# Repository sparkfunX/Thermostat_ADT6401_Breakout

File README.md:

SparkFun Auto-Digital Thermostat - ADT6401
=============================

New from SparkX, the ADT6401 breakout board. This IC triggers alarm pin and LED when the temperature reading crosses a temperature trip point. Set the trip point easily using the SPDT switches included on the breakout.

SparkFun labored with love to design this board. Feel like supporting open-source hardware?
Buy a [board](https://www.sparkfun.com/) from SparkFun!

Repository Contents
-------------------

* **/Documents** - Datasheet for the ADT6401 IC.
* **/Hardware** - Eagle design files (.brd, .sch).
* **/Production** - Production panel files (.brd).

License Information
-------------------

This product is _**open source**_!

Please review the LICENSE.md file for license information.

If you have any questions or concerns regarding our licensing, please contact technical support on our [SparkFun Forum](https://www.sparkfun.com/viewforum.php?f=152).

Distributed as-is; no warranty is given.

- Your friends at SparkFun

_<COLLABORATION CREDIT>_

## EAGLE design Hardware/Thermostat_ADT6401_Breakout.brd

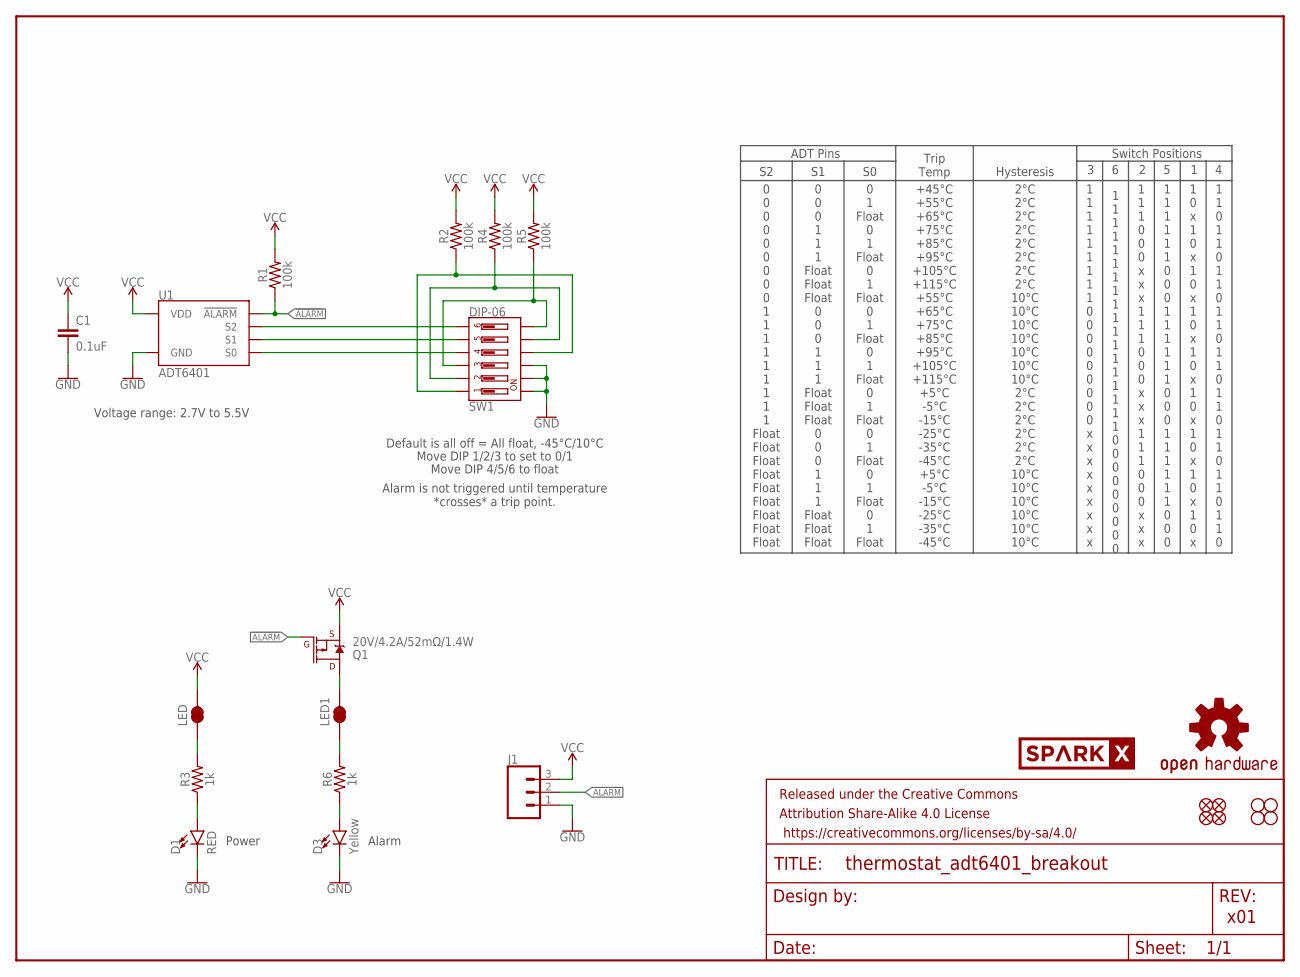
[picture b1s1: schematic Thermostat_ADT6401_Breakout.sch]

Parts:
C1: 0.1uF; 0603
D1: RED; LED-0603
D3: Yellow; LED-0603
FRAME1: FRAME-LETTER; CREATIVE_COMMONS
J1: CONN_031X03_NO_SILK; 1X03_NO_SILK
JP1, JP2, JP5, JP6: FIDUCIAL1X2; FIDUCIAL-1X2
JP3, JP4, JP8, JP9: STAND-OFF
LED, LED1: JUMPER-SMT_2_NC_TRACE_SILK; SMT-JUMPER_2_NC_TRACE_SILK
LOGO1: OSHW-LOGOMINI; OSHW-LOGO-MINI
Q1: 20V/4.2A/52mΩ/1.4W; SOT23-3
R1, R2, R4, R5: 100k; 0603
R3, R6: 1k; 0603
SW1: DIP-06; DIPSWITCH-06-SMD
U1: ADT6401; SOT23-6
U$1: SPARKX-LOGO4; SPARKX-MEDIUM

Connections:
!ALARM!: J1.2, Q1.1 (G), R1.1, U1.6 (!ALARM!)
GND: C1.2, D1.C, D3.C, J1.1, SW1.10, SW1.11, SW1.12, U1.5 (GND)
unnamed: D1.A, R3.1
unnamed: LED.1, R3.2
unnamed: LED1.2, Q1.3 (D)
unnamed: D3.A, R6.1
unnamed: LED1.1, R6.2
S0: SW1.4, U1.3 (S0)
S0_PU: R2.1, SW1.1, SW1.9
S1: SW1.5, U1.2 (S1)
S1_PU: R4.1, SW1.2, SW1.8
S2: SW1.6, U1.1 (S2)
S2_PU: R5.1, SW1.3, SW1.7
VCC: C1.1, J1.3, LED.2, Q1.2 (S), R1.2, R2.2, R4.2, R5.2, U1.4 (VDD)

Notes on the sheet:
x01
Power
Move DIP 4/5/6 to float
0 0 0 0 0 0 0 0 0 1 1 1 1 1 1 1 1 1 Float Float Float Float Float Float Float Float Float
+45°C +55°C +65°C +75°C +85°C +95°C +105°C +115°C +55°C +65°C +75°C +85°C +95°C +105°C +115°C +5°C -5°C -15°C -25°C -35°C -45°C +5°C -5°C -15°C -25°C -35°C -45°C
0 0 0 1 1 1 Float Float Float 0 0 0 1 1 1 Float Float Float 0 0 0 1 1 1 Float Float Float
0 1 Float 0 1 Float 0 1 Float 0 1 Float 0 1 Float 0 1 Float 0 1 Float 0 1 Float 0 1 Float
2°C 2°C 2°C 2°C 2°C 2°C 2°C 2°C 10°C 10°C 10°C 10°C 10°C 10°C 10°C 2°C 2°C 2°C 2°C 2°C 2°C 10°C 10°C 10°C 10°C 10°C 10°C
Trip Temp
Hysteresis
Move DIP 1/2/3 to set to 0/1
Default is all off = All float, -45°C/10°C
Alarm
Voltage range: 2.7V to 5.5V
Switch Positions
1 1 0 1 1 0 1 1 0 1 1 0 1 1 0 1 1 0 1 1 0 1 1 0 1 1 0
1 0 x 1 0 x 1 0 x 1 0 x 1 0 x 1 0 x 1 0 x 1 0 x 1 0 x
1 1 1 1 1 1 0 0 0 1 1 1 1 1 1 0 0 0 1 1 1 1 1 1 0 0 0
1 1 1 0 0 0 x x x 1 1 1 0 0 0 x x x 1 1 1 0 0 0 x x x
1 1 1 1 1 1 1 1 1 1 1 1 1 1 1 1 1 1 0 0 0 0 0 0 0 0 0
1 1 1 1 1 1 1 1 1 0 0 0 0 0 0 0 0 0 x x x x x x x x x
ADT Pins
Alarm is not triggered until temperature *crosses* a trip point.

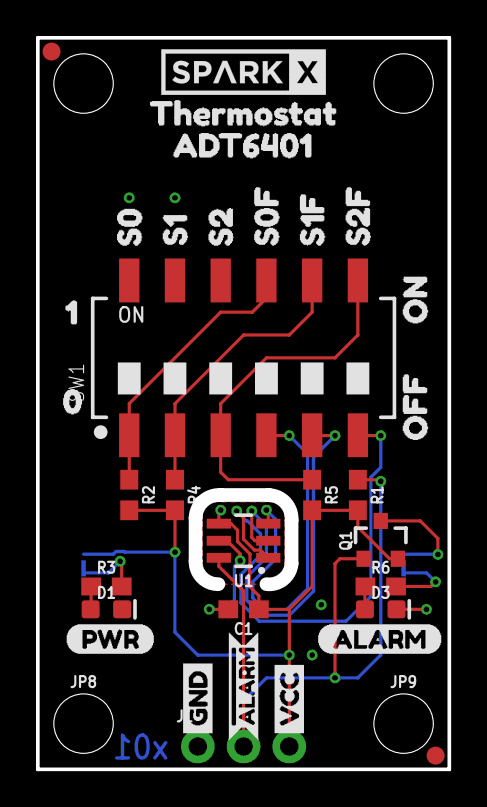
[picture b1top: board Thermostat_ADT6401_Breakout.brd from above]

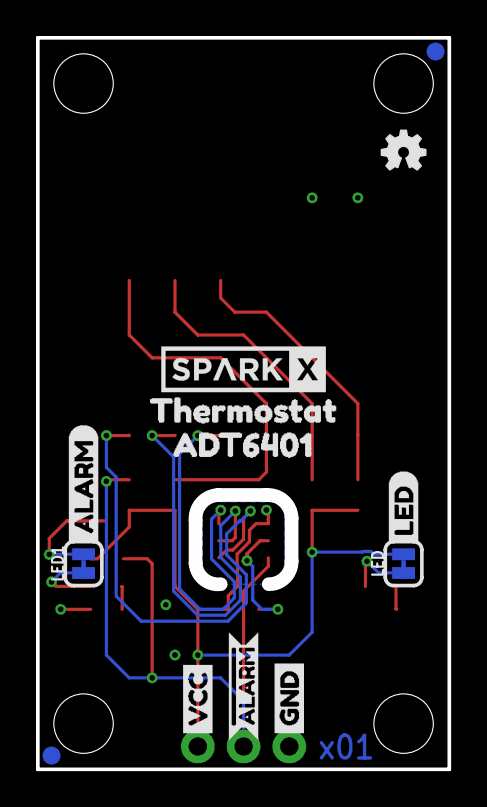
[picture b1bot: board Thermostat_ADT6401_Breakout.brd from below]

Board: 2 copper layers, 22.3 x 40.1 mm, 52 parts (13 on the bottom side), 14 nets.

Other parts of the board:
U$2: 01
U$3, U$15: #ALARM6
U$4, U$12: ADT64012
U$5, U$13: GND6
U$6: OFF3
U$7: ON2
U$8: 10
U$9, U$19: THERMOSTAT0
U$10: (PWR)
U$11, U$16: VCC5
U$14: S1F5
U$17: SPARKX-LOGO4; SPARKX-MEDIUM
U$18: ORDERING_INSTRUCTIONS
U$20: ALARM1
U$21: S2F7
U$22: S12
U$23: S23
U$24: S00
U$25: S0F1
U$26: LED0
U$27: ALARM2

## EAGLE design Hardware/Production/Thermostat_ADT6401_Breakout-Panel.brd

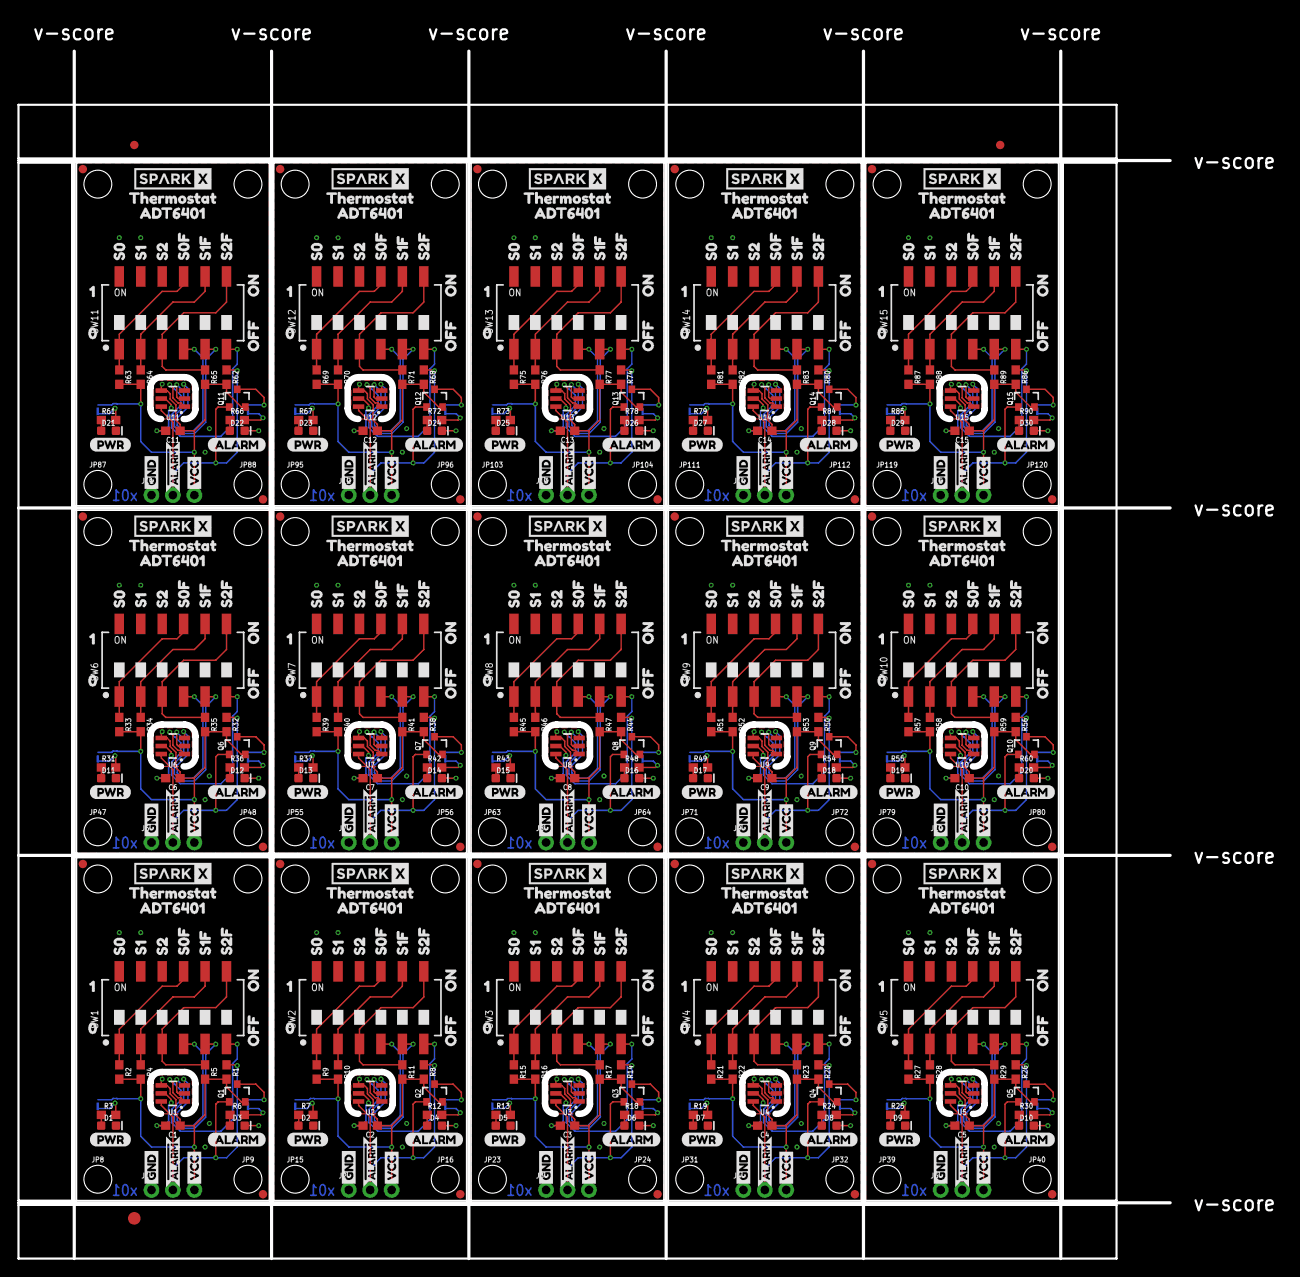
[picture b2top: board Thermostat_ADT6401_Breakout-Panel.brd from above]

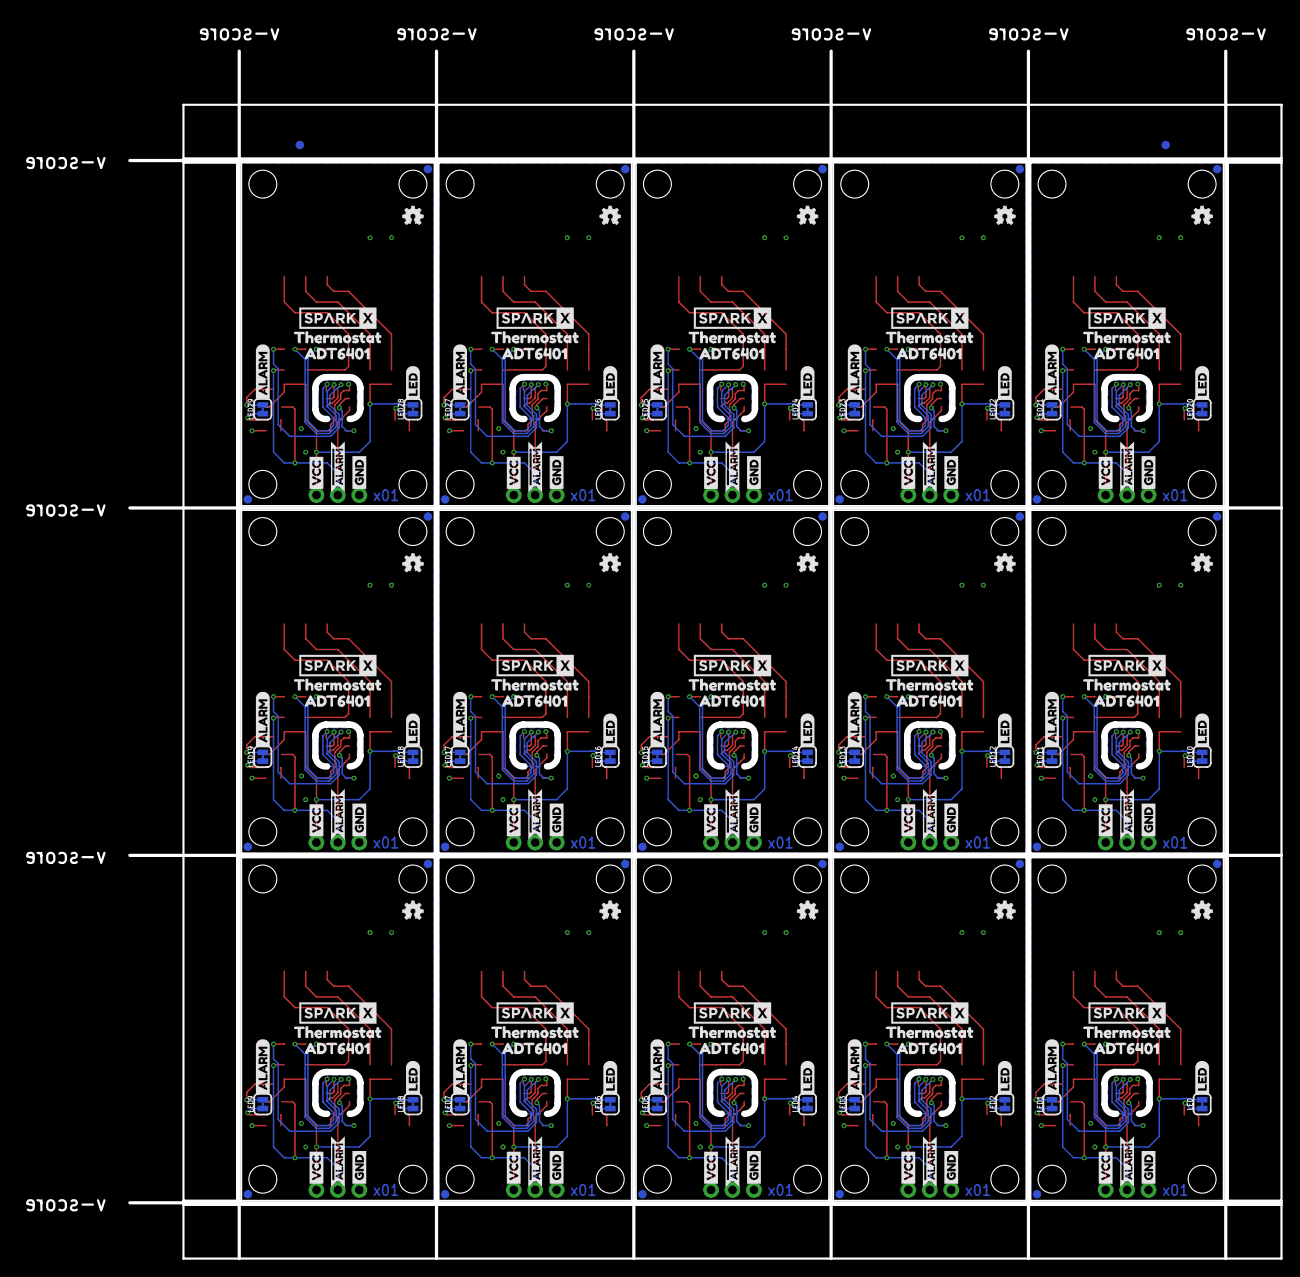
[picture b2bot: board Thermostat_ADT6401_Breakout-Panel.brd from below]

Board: 2 copper layers, 149.2 x 146.5 mm, 755 parts (197 on the bottom side), 210 nets.

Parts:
C1, C2, C3, C4, C5, C6, C7, C8, C9, C10, C11, C12, C13, C14, C15: 0.1uF; 0603
D1, D2, D5, D7, D9, D11, D13, D15, D17, D19, D21, D23, D25, D27, D29: RED; LED-0603
D3, D4, D6, D8, D10, D12, D14, D16, D18, D20, D22, D24, D26, D28, D30: Yellow; LED-0603
E$1, E$2, E$3, E$4: FIDUCIAL-1X2
E$5: FIDUCIAL-1.5X3
J1, J2, J3, J4, J5, J6, J7, J8, J9, J10, J11, J12, J13, J14, J15: 1X03_NO_SILK
JP1, JP2, JP5, JP6, JP11, JP12, JP13, JP14, JP19, JP20, JP21, JP22, JP27, JP28, JP29, JP30, JP35, JP36, JP37, JP38, JP43, JP44, JP45, JP46, JP51, JP52, JP53, JP54, JP59, JP60, JP61, JP62, JP67, JP68, JP69, JP70, JP75, JP76, JP77, JP78, JP83, JP84, JP85, JP86, JP91, JP92, JP93, JP94, JP99, JP100, JP101, JP102, JP107, JP108, JP109, JP110, JP115, JP116, JP117, JP118: FIDUCIAL1X2; FIDUCIAL-1X2
JP3, JP4, JP7, JP8, JP9, JP10, JP15, JP16, JP17, JP18, JP23, JP24, JP25, JP26, JP31, JP32, JP33, JP34, JP39, JP40, JP41, JP42, JP47, JP48, JP49, JP50, JP55, JP56, JP57, JP58, JP63, JP64, JP65, JP66, JP71, JP72, JP73, JP74, JP79, JP80, JP81, JP82, JP87, JP88, JP89, JP90, JP95, JP96, JP97, JP98, JP103, JP104, JP105, JP106, JP111, JP112, JP113, JP114, JP119, JP120: STAND-OFF
LED, LED1, LED2, LED3, LED4, LED5, LED6, LED7, LED8, LED9, LED10, LED11, LED12, LED13, LED14, LED15, LED16, LED17, LED18, LED19, LED20, LED21, LED22, LED23, LED24, LED25, LED26, LED27, LED28, LED29: SMT-JUMPER_2_NC_TRACE_SILK
LOGO1, LOGO2, LOGO3, LOGO4, LOGO5, LOGO6, LOGO7, LOGO8, LOGO9, LOGO10, LOGO11, LOGO12, LOGO13, LOGO14, LOGO15: OSHW-LOGOMINI; OSHW-LOGO-MINI
Q1, Q2, Q3, Q4, Q5, Q6, Q7, Q8, Q9, Q10, Q11, Q12, Q13, Q14, Q15: 20V/4.2A/52mΩ/1.4W; SOT23-3
R1, R2, R4, R5, R8, R9, R10, R11, R14, R15, R16, R17, R20, R21, R22, R23, R26, R27, R28, R29, R32, R33, R34, R35, R38, R39, R40, R41, R44, R45, R46, R47, R50, R51, R52, R53, R56, R57, R58, R59, R62, R63, R64, R65, R68, R69, R70, R71, R74, R75, R76, R77, R80, R81, R82, R83, R86, R87, R88, R89: 100k; 0603
R3, R6, R7, R12, R13, R18, R19, R24, R25, R30, R31, R36, R37, R42, R43, R48, R49, R54, R55, R60, R61, R66, R67, R72, R73, R78, R79, R84, R85, R90: 1k; 0603
SW1, SW2, SW3, SW4, SW5, SW6, SW7, SW8, SW9, SW10, SW11, SW12, SW13, SW14, SW15: DIP-06; DIPSWITCH-06-SMD
U1, U2, U3, U4, U5, U6, U7, U8, U9, U10, U11, U12, U13, U14, U15: ADT6401; SOT23-6
U$1, U$17, U$18, U$36, U$53, U$62, U$79, U$88, U$105, U$114, U$131, U$140, U$157, U$166, U$183, U$192, U$209, U$218, U$235, U$244, U$261, U$270, U$287, U$296, U$313, U$322, U$339, U$348, U$365, U$374: SPARKX-LOGO4; SPARKX-MEDIUM
U$2, U$40, U$66, U$92, U$118, U$144, U$170, U$196, U$222, U$248, U$274, U$300, U$326, U$352, U$378: 01
U$3, U$15, U$38, U$39, U$64, U$65, U$90, U$91, U$116, U$117, U$142, U$143, U$168, U$169, U$194, U$195, U$220, U$221, U$246, U$247, U$272, U$273, U$298, U$299, U$324, U$325, U$350, U$351, U$376, U$377: #ALARM6
U$4, U$12, U$49, U$50, U$75, U$76, U$101, U$102, U$127, U$128, U$153, U$154, U$179, U$180, U$205, U$206, U$231, U$232, U$257, U$258, U$283, U$284, U$309, U$310, U$335, U$336, U$361, U$362, U$387, U$388: ADT64012
U$5, U$13, U$29, U$34, U$55, U$60, U$81, U$86, U$107, U$112, U$133, U$138, U$159, U$164, U$185, U$190, U$211, U$216, U$237, U$242, U$263, U$268, U$289, U$294, U$315, U$320, U$341, U$346, U$367, U$372: GND6
U$6, U$30, U$56, U$82, U$108, U$134, U$160, U$186, U$212, U$238, U$264, U$290, U$316, U$342, U$368: OFF3
U$7, U$31, U$57, U$83, U$109, U$135, U$161, U$187, U$213, U$239, U$265, U$291, U$317, U$343, U$369: ON2
U$8, U$41, U$67, U$93, U$119, U$145, U$171, U$197, U$223, U$249, U$275, U$301, U$327, U$353, U$379: 10
U$9, U$19, U$32, U$37, U$58, U$63, U$84, U$89, U$110, U$115, U$136, U$141, U$162, U$167, U$188, U$193, U$214, U$219, U$240, U$245, U$266, U$271, U$292, U$297, U$318, U$323, U$344, U$349, U$370, U$375: THERMOSTAT0
U$10, U$28, U$54, U$80, U$106, U$132, U$158, U$184, U$210, U$236, U$262, U$288, U$314, U$340, U$366: (PWR)
U$11, U$16, U$33, U$35, U$59, U$61, U$85, U$87, U$111, U$113, U$137, U$139, U$163, U$165, U$189, U$191, U$215, U$217, U$241, U$243, U$267, U$269, U$293, U$295, U$319, U$321, U$345, U$347, U$371, U$373: VCC5
U$14, U$42, U$68, U$94, U$120, U$146, U$172, U$198, U$224, U$250, U$276, U$302, U$328, U$354, U$380: S1F5
U$20, U$51, U$77, U$103, U$129, U$155, U$181, U$207, U$233, U$259, U$285, U$311, U$337, U$363, U$389: ALARM1
U$21, U$43, U$69, U$95, U$121, U$147, U$173, U$199, U$225, U$251, U$277, U$303, U$329, U$355, U$381: S2F7
U$22, U$44, U$70, U$96, U$122, U$148, U$174, U$200, U$226, U$252, U$278, U$304, U$330, U$356, U$382: S12
U$23, U$45, U$71, U$97, U$123, U$149, U$175, U$201, U$227, U$253, U$279, U$305, U$331, U$357, U$383: S23
U$24, U$46, U$72, U$98, U$124, U$150, U$176, U$202, U$228, U$254, U$280, U$306, U$332, U$358, U$384: S00
U$25, U$47, U$73, U$99, U$125, U$151, U$177, U$203, U$229, U$255, U$281, U$307, U$333, U$359, U$385: S0F1
U$26, U$52, U$78, U$104, U$130, U$156, U$182, U$208, U$234, U$260, U$286, U$312, U$338, U$364, U$390: LED0
U$27, U$48, U$74, U$100, U$126, U$152, U$178, U$204, U$230, U$256, U$282, U$308, U$334, U$360, U$386: ALARM2

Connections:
!ALARM!: J1.2, Q1.1, R1.1, U1.6
!ALARM!1: J2.2, Q2.1, R8.1, U2.6
!ALARM!2: J3.2, Q3.1, R14.1, U3.6
!ALARM!3: J4.2, Q4.1, R20.1, U4.6
!ALARM!4: J5.2, Q5.1, R26.1, U5.6
!ALARM!5: J6.2, Q6.1, R32.1, U6.6
!ALARM!6: J7.2, Q7.1, R38.1, U7.6
!ALARM!7: J8.2, Q8.1, R44.1, U8.6
!ALARM!8: J9.2, Q9.1, R50.1, U9.6
!ALARM!9: J10.2, Q10.1, R56.1, U10.6
!ALARM!10: J11.2, Q11.1, R62.1, U11.6
!ALARM!11: J12.2, Q12.1, R68.1, U12.6
!ALARM!12: J13.2, Q13.1, R74.1, U13.6
!ALARM!13: J14.2, Q14.1, R80.1, U14.6
!ALARM!14: J15.2, Q15.1, R86.1, U15.6
GND: C1.2, D1.C, D3.C, J1.1, SW1.10, SW1.11, SW1.12, U1.5
GND1: C2.2, D2.C, D4.C, J2.1, SW2.10, SW2.11, SW2.12, U2.5
GND2: C3.2, D5.C, D6.C, J3.1, SW3.10, SW3.11, SW3.12, U3.5
GND3: C4.2, D7.C, D8.C, J4.1, SW4.10, SW4.11, SW4.12, U4.5
GND4: C5.2, D9.C, D10.C, J5.1, SW5.10, SW5.11, SW5.12, U5.5
GND5: C6.2, D11.C, D12.C, J6.1, SW6.10, SW6.11, SW6.12, U6.5
GND6: C7.2, D13.C, D14.C, J7.1, SW7.10, SW7.11, SW7.12, U7.5
GND7: C8.2, D15.C, D16.C, J8.1, SW8.10, SW8.11, SW8.12, U8.5
GND8: C9.2, D17.C, D18.C, J9.1, SW9.10, SW9.11, SW9.12, U9.5
GND9: C10.2, D19.C, D20.C, J10.1, SW10.10, SW10.11, SW10.12, U10.5
GND10: C11.2, D21.C, D22.C, J11.1, SW11.10, SW11.11, SW11.12, U11.5
GND11: C12.2, D23.C, D24.C, J12.1, SW12.10, SW12.11, SW12.12, U12.5
GND12: C13.2, D25.C, D26.C, J13.1, SW13.10, SW13.11, SW13.12, U13.5
GND13: C14.2, D27.C, D28.C, J14.1, SW14.10, SW14.11, SW14.12, U14.5
GND14: C15.2, D29.C, D30.C, J15.1, SW15.10, SW15.11, SW15.12, U15.5
unnamed: D2.A, R7.1
unnamed: LED2.1, R7.2
unnamed: D1.A, R3.1
unnamed: LED.1, R3.2
unnamed: LED1.2, Q1.3
unnamed: D3.A, R6.1
unnamed: LED1.1, R6.2
unnamed: LED3.2, Q2.3
unnamed: D4.A, R12.1
unnamed: LED3.1, R12.2
unnamed: D5.A, R13.1
unnamed: LED4.1, R13.2
unnamed: LED5.2, Q3.3
unnamed: D6.A, R18.1
unnamed: LED5.1, R18.2
unnamed: D7.A, R19.1
unnamed: LED6.1, R19.2
unnamed: LED7.2, Q4.3
unnamed: D8.A, R24.1
unnamed: LED7.1, R24.2
unnamed: D9.A, R25.1
unnamed: LED8.1, R25.2
unnamed: LED9.2, Q5.3
unnamed: D10.A, R30.1
unnamed: LED9.1, R30.2
unnamed: D11.A, R31.1
unnamed: LED10.1, R31.2
unnamed: LED11.2, Q6.3
unnamed: D12.A, R36.1
unnamed: LED11.1, R36.2
unnamed: D13.A, R37.1
unnamed: LED12.1, R37.2
unnamed: LED13.2, Q7.3
unnamed: D14.A, R42.1
unnamed: LED13.1, R42.2
unnamed: D15.A, R43.1
unnamed: LED14.1, R43.2
unnamed: LED15.2, Q8.3
unnamed: D16.A, R48.1
unnamed: LED15.1, R48.2
unnamed: D17.A, R49.1
unnamed: LED16.1, R49.2
unnamed: LED17.2, Q9.3
unnamed: D18.A, R54.1
unnamed: LED17.1, R54.2
unnamed: D19.A, R55.1
unnamed: LED18.1, R55.2
unnamed: LED19.2, Q10.3
unnamed: D20.A, R60.1
unnamed: LED19.1, R60.2
unnamed: D21.A, R61.1
unnamed: LED20.1, R61.2
unnamed: LED21.2, Q11.3
unnamed: D22.A, R66.1
unnamed: LED21.1, R66.2
unnamed: D23.A, R67.1
unnamed: LED22.1, R67.2
unnamed: LED23.2, Q12.3
unnamed: D24.A, R72.1
unnamed: LED23.1, R72.2
unnamed: D25.A, R73.1
unnamed: LED24.1, R73.2
unnamed: LED25.2, Q13.3
unnamed: D26.A, R78.1
unnamed: LED25.1, R78.2
unnamed: D27.A, R79.1
unnamed: LED26.1, R79.2
unnamed: LED27.2, Q14.3
unnamed: D28.A, R84.1
unnamed: LED27.1, R84.2
unnamed: D29.A, R85.1
unnamed: LED28.1, R85.2
unnamed: LED29.2, Q15.3
unnamed: D30.A, R90.1
unnamed: LED29.1, R90.2
S0: SW1.4, U1.3
S0_PU: R2.1, SW1.1, SW1.9
S0_PU1: R9.1, SW2.1, SW2.9
S0_PU2: R15.1, SW3.1, SW3.9
S0_PU3: R21.1, SW4.1, SW4.9
S0_PU4: R27.1, SW5.1, SW5.9
S0_PU5: R33.1, SW6.1, SW6.9
S0_PU6: R39.1, SW7.1, SW7.9
S0_PU7: R45.1, SW8.1, SW8.9
S0_PU8: R51.1, SW9.1, SW9.9
S0_PU9: R57.1, SW10.1, SW10.9
S0_PU10: R63.1, SW11.1, SW11.9
S0_PU11: R69.1, SW12.1, SW12.9
S0_PU12: R75.1, SW13.1, SW13.9
S0_PU13: R81.1, SW14.1, SW14.9
S0_PU14: R87.1, SW15.1, SW15.9
S1: SW1.5, U1.2
S1_PU: R4.1, SW1.2, SW1.8
S1_PU1: R10.1, SW2.2, SW2.8
S1_PU2: R16.1, SW3.2, SW3.8
S1_PU3: R22.1, SW4.2, SW4.8
S1_PU4: R28.1, SW5.2, SW5.8
S1_PU5: R34.1, SW6.2, SW6.8
S1_PU6: R40.1, SW7.2, SW7.8
S1_PU7: R46.1, SW8.2, SW8.8
S1_PU8: R52.1, SW9.2, SW9.8
S1_PU9: R58.1, SW10.2, SW10.8
S1_PU10: R64.1, SW11.2, SW11.8
S1_PU11: R70.1, SW12.2, SW12.8
S1_PU12: R76.1, SW13.2, SW13.8
S1_PU13: R82.1, SW14.2, SW14.8
S1_PU14: R88.1, SW15.2, SW15.8
S2: SW1.6, U1.1
S2_PU: R5.1, SW1.3, SW1.7
S2_PU1: R11.1, SW2.3, SW2.7
S2_PU2: R17.1, SW3.3, SW3.7
S2_PU3: R23.1, SW4.3, SW4.7
S2_PU4: R29.1, SW5.3, SW5.7
S2_PU5: R35.1, SW6.3, SW6.7
S2_PU6: R41.1, SW7.3, SW7.7
S2_PU7: R47.1, SW8.3, SW8.7
S2_PU8: R53.1, SW9.3, SW9.7
S2_PU9: R59.1, SW10.3, SW10.7
S2_PU10: R65.1, SW11.3, SW11.7
S2_PU11: R71.1, SW12.3, SW12.7
S2_PU12: R77.1, SW13.3, SW13.7
S2_PU13: R83.1, SW14.3, SW14.7
S2_PU14: R89.1, SW15.3, SW15.7
S3: SW2.4, U2.3
S4: SW2.5, U2.2
S5: SW2.6, U2.1
S6: SW3.4, U3.3
S7: SW3.5, U3.2
S8: SW3.6, U3.1
S9: SW4.4, U4.3
S10: SW4.5, U4.2
S11: SW4.6, U4.1
S12: SW5.4, U5.3
S13: SW5.5, U5.2
S14: SW5.6, U5.1
S15: SW6.4, U6.3
S16: SW6.5, U6.2
S17: SW6.6, U6.1
S18: SW7.4, U7.3
S19: SW7.5, U7.2
S20: SW7.6, U7.1
S21: SW8.4, U8.3
S22: SW8.5, U8.2
S23: SW8.6, U8.1
S24: SW9.4, U9.3
S25: SW9.5, U9.2
S26: SW9.6, U9.1
S27: SW10.4, U10.3
S28: SW10.5, U10.2
S29: SW10.6, U10.1
S30: SW11.4, U11.3
S31: SW11.5, U11.2
S32: SW11.6, U11.1
S33: SW12.4, U12.3
S34: SW12.5, U12.2
S35: SW12.6, U12.1
S36: SW13.4, U13.3
S37: SW13.5, U13.2
S38: SW13.6, U13.1
S39: SW14.4, U14.3
S40: SW14.5, U14.2
S41: SW14.6, U14.1
S42: SW15.4, U15.3
S43: SW15.5, U15.2
S44: SW15.6, U15.1
VCC: C1.1, J1.3, LED.2, Q1.2, R1.2, R2.2, R4.2, R5.2, U1.4
VCC1: C2.1, J2.3, LED2.2, Q2.2, R8.2, R9.2, R10.2, R11.2, U2.4
VCC2: C3.1, J3.3, LED4.2, Q3.2, R14.2, R15.2, R16.2, R17.2, U3.4
VCC3: C4.1, J4.3, LED6.2, Q4.2, R20.2, R21.2, R22.2, R23.2, U4.4
VCC4: C5.1, J5.3, LED8.2, Q5.2, R26.2, R27.2, R28.2, R29.2, U5.4
VCC5: C6.1, J6.3, LED10.2, Q6.2, R32.2, R33.2, R34.2, R35.2, U6.4
VCC6: C7.1, J7.3, LED12.2, Q7.2, R38.2, R39.2, R40.2, R41.2, U7.4
VCC7: C8.1, J8.3, LED14.2, Q8.2, R44.2, R45.2, R46.2, R47.2, U8.4
VCC8: C9.1, J9.3, LED16.2, Q9.2, R50.2, R51.2, R52.2, R53.2, U9.4
VCC9: C10.1, J10.3, LED18.2, Q10.2, R56.2, R57.2, R58.2, R59.2, U10.4
VCC10: C11.1, J11.3, LED20.2, Q11.2, R62.2, R63.2, R64.2, R65.2, U11.4
VCC11: C12.1, J12.3, LED22.2, Q12.2, R68.2, R69.2, R70.2, R71.2, U12.4
VCC12: C13.1, J13.3, LED24.2, Q13.2, R74.2, R75.2, R76.2, R77.2, U13.4
VCC13: C14.1, J14.3, LED26.2, Q14.2, R80.2, R81.2, R82.2, R83.2, U14.4
VCC14: C15.1, J15.3, LED28.2, Q15.2, R86.2, R87.2, R88.2, R89.2, U15.4

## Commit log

2020-08-18 Remove old files
2020-08-20 Add voltage range
2020-08-24 Update SPDT chart
2020-08-24 Update SPDT chart pt 2
2020-08-24 Combine switches into chart. Add ignore. Remove old files.
2020-08-24 Adding product page files
2020-11-20 Create License.md
    Added License

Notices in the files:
parts and their libraries:
SparkFun-Resistors: Licensing: Creative Commons ShareAlike 4.0 International - https://creativecommons.org/licenses/by-sa/4.0
SparkFun-Aesthetics: Released under the Creative Commons Attribution Share-Alike 4.0 License
SparkFun-Aesthetics: https://creativecommons.org/licenses/by-sa/4.0
